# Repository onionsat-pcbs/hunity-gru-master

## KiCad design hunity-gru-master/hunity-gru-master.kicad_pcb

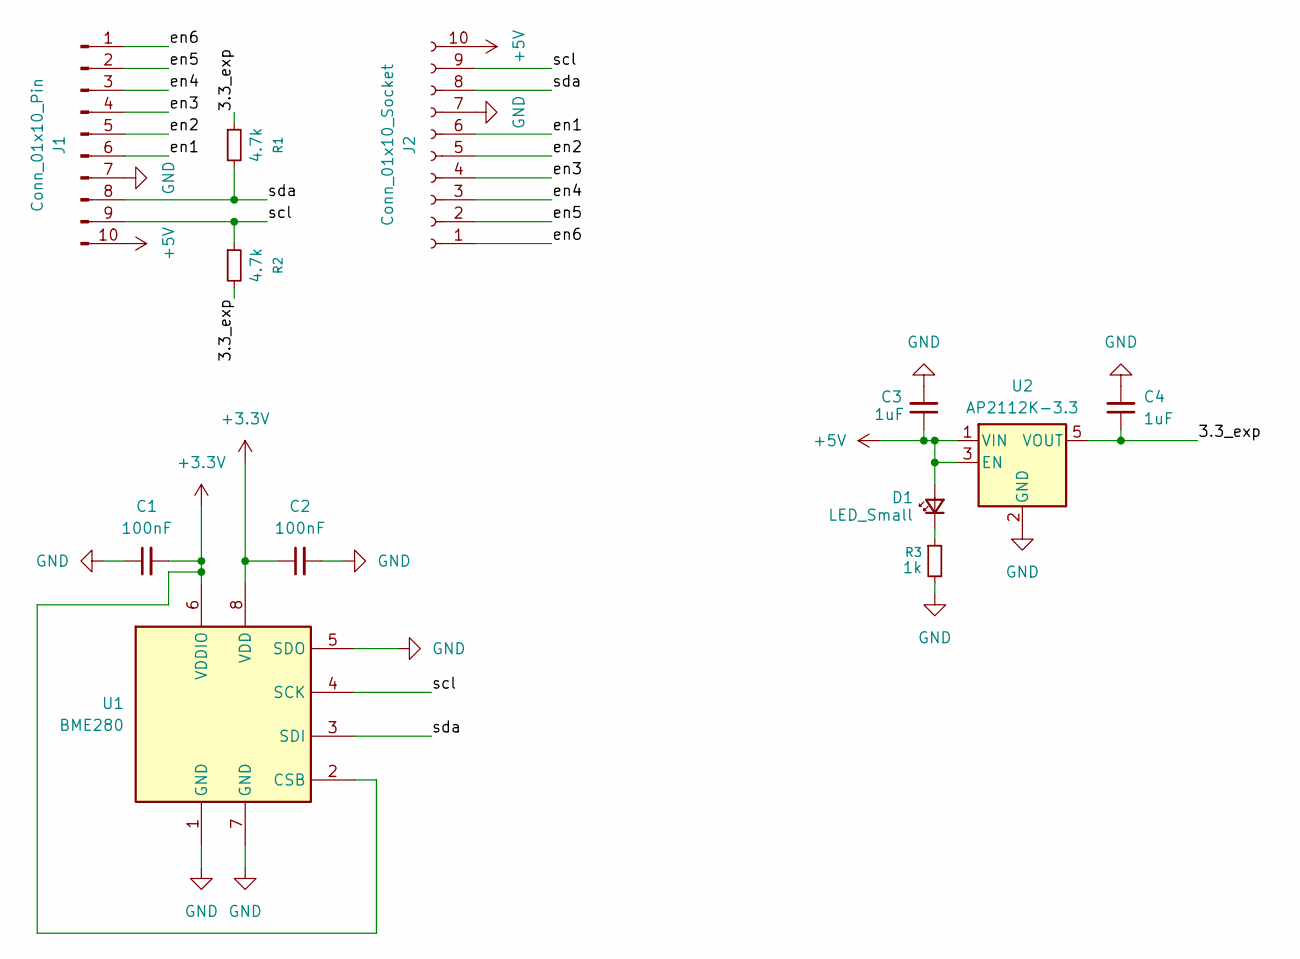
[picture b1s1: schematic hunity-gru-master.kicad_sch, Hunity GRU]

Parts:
C1, C2: 100nF; C_0603_1608Metric
C3, C4: 1uF; C_0603_1608Metric
D1: LED_Small; LED_0603_1608Metric
J1: Conn_01x10_Pin; header
J2: Conn_01x10_Socket; socket
R1, R2: 4.7k; R_0603_1608Metric
R3: 1k; R_0603_1608Metric
U1: BME280; Bosch_LGA-8_2.5x2.5mm_P0.65mm_ClockwisePinNumbering
U2: AP2112K-3.3; SOT-23-5

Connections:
+3.3V: C1.2, C2.1, U1.2 (CSB), U1.6 (VDDIO), U1.8 (VDD)
+5V: C3.1, D1.2 (A), J1.10, J2.10, U2.1 (VIN), U2.3 (EN)
/3.3_exp: C4.1, R1.1, R2.2, U2.5 (VOUT)
/en1: J1.6, J2.6
/en2: J1.5, J2.5
/en3: J1.4, J2.4
/en4: J1.3, J2.3
/en5: J1.2, J2.2
/en6: J1.1, J2.1
/scl: J1.9, J2.9, R2.1, U1.4 (SCK)
/sda: J1.8, J2.8, R1.2, U1.3 (SDI)
GND: C1.1, C2.2, C3.2, C4.2, J1.7, J2.7, R3.2, U1.1 (GND), U1.5 (SDO), U1.7 (GND), U2.2 (GND)
unnamed: D1.1 (K), R3.1

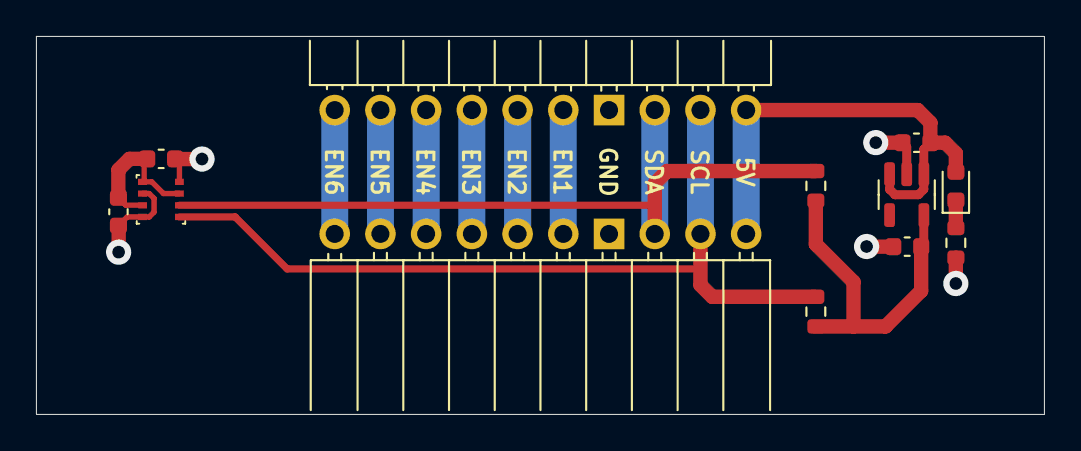
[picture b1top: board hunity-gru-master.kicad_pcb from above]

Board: 2 copper layers, 56.0 x 21.0 mm, 12 parts (0 on the bottom side), 13 nets.

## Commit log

2025-05-29 initial release
2025-05-29 labelling+generating production files
2025-05-29 production zip
